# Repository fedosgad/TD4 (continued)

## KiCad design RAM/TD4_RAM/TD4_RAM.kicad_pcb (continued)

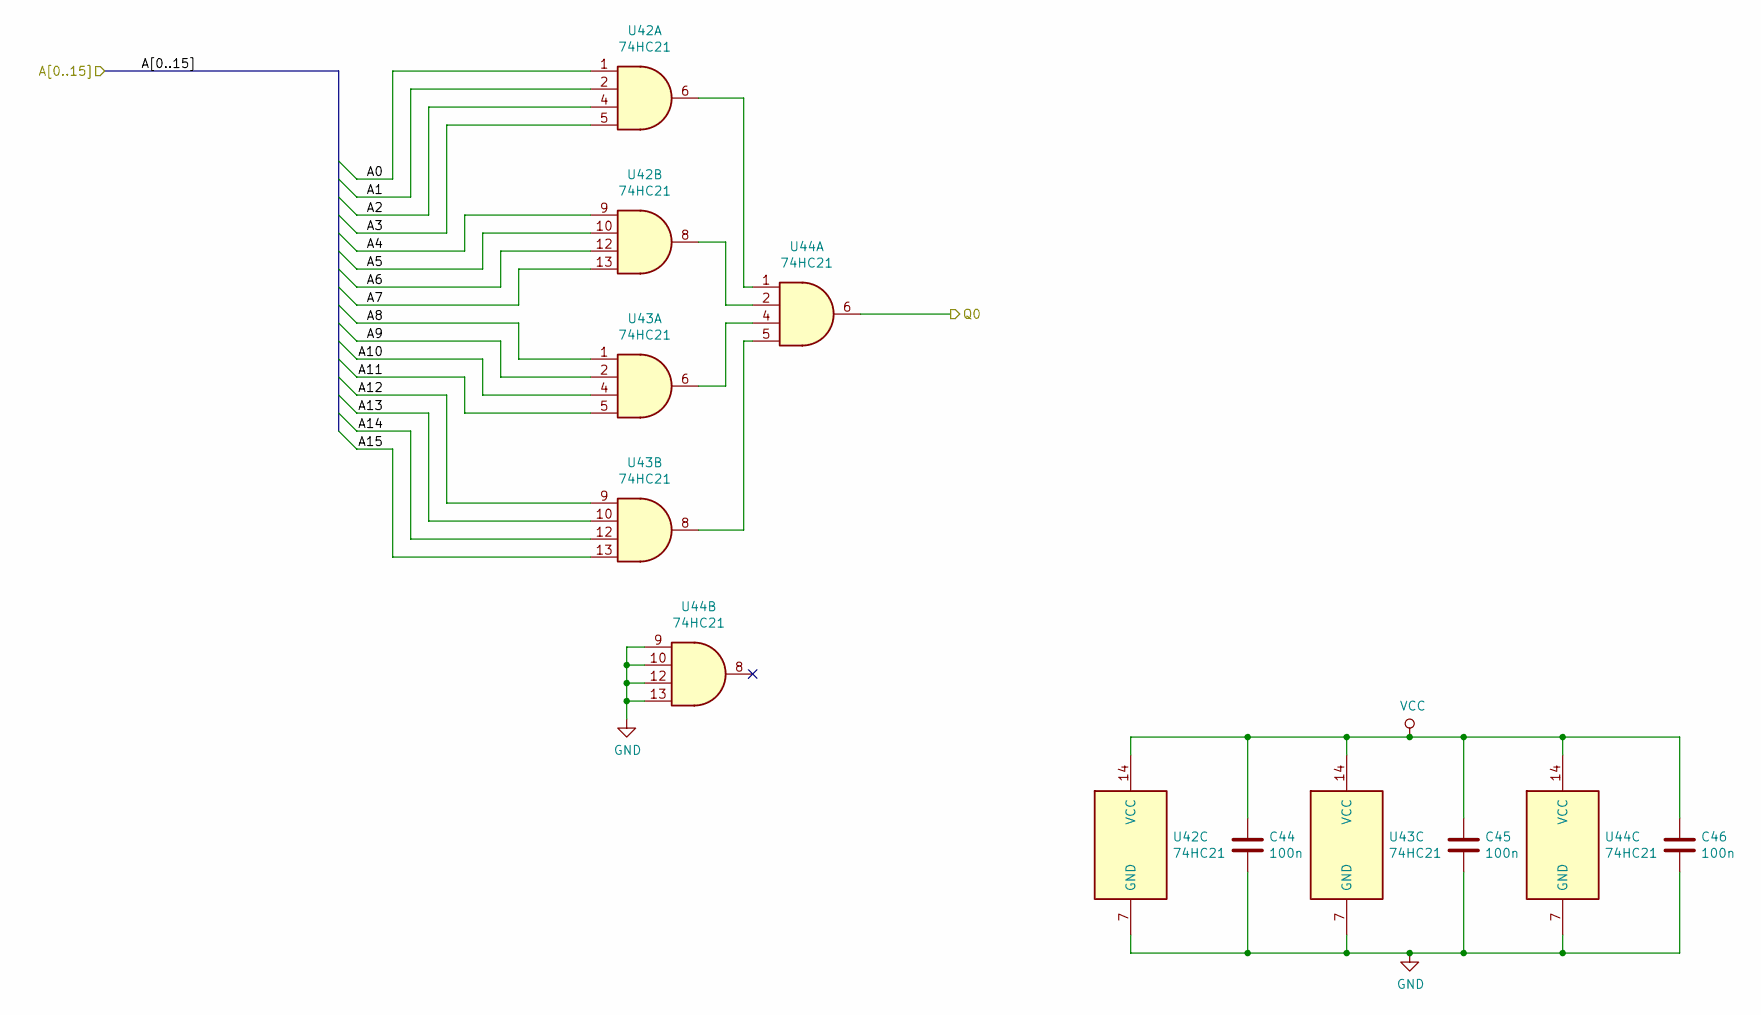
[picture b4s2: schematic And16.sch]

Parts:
C44, C45, C46: 100n; C_0805_2012Metric
U42, U43, U44: 74HC21; SOIC-14_3.9x8.7mm_P1.27mm

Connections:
/sheet5CBA2603/A0: U42.1; also elsewhere on the board
/sheet5CBA2603/A1: U42.2; also elsewhere on the board
/sheet5CBA2603/A2: U42.4; also elsewhere on the board
/sheet5CBA2603/A3: U42.5; also elsewhere on the board
/sheet5CBA2603/A4: U42.9; also elsewhere on the board
/sheet5CBA2603/A5: U42.10; also elsewhere on the board
/sheet5CBA2603/A6: U42.12; also elsewhere on the board
/sheet5CBA2603/A7: U42.13; also elsewhere on the board
/sheet5CBA2603/A8: U43.1; also elsewhere on the board
/sheet5CBA2603/A9: U43.2; also elsewhere on the board
/sheet5CBA2603/A10: U43.4; also elsewhere on the board
/sheet5CBA2603/A11: U43.5; also elsewhere on the board
/sheet5CBA2603/A12: U43.9; also elsewhere on the board
/sheet5CBA2603/A13: U43.10; also elsewhere on the board
/sheet5CBA2603/A14: U43.12; also elsewhere on the board
/sheet5CBA2603/A15: U43.13; also elsewhere on the board
/sheet5CBA2603/Q0: U44.6; also elsewhere on the board
unnamed: U42.6, U44.1
unnamed: U42.8, U44.2
unnamed: U43.6, U44.4
unnamed: U43.8, U44.5
VCC: C44.1, C45.1, C46.1, U42.14 (VCC), U43.14 (VCC), U44.14 (VCC); also elsewhere on the board

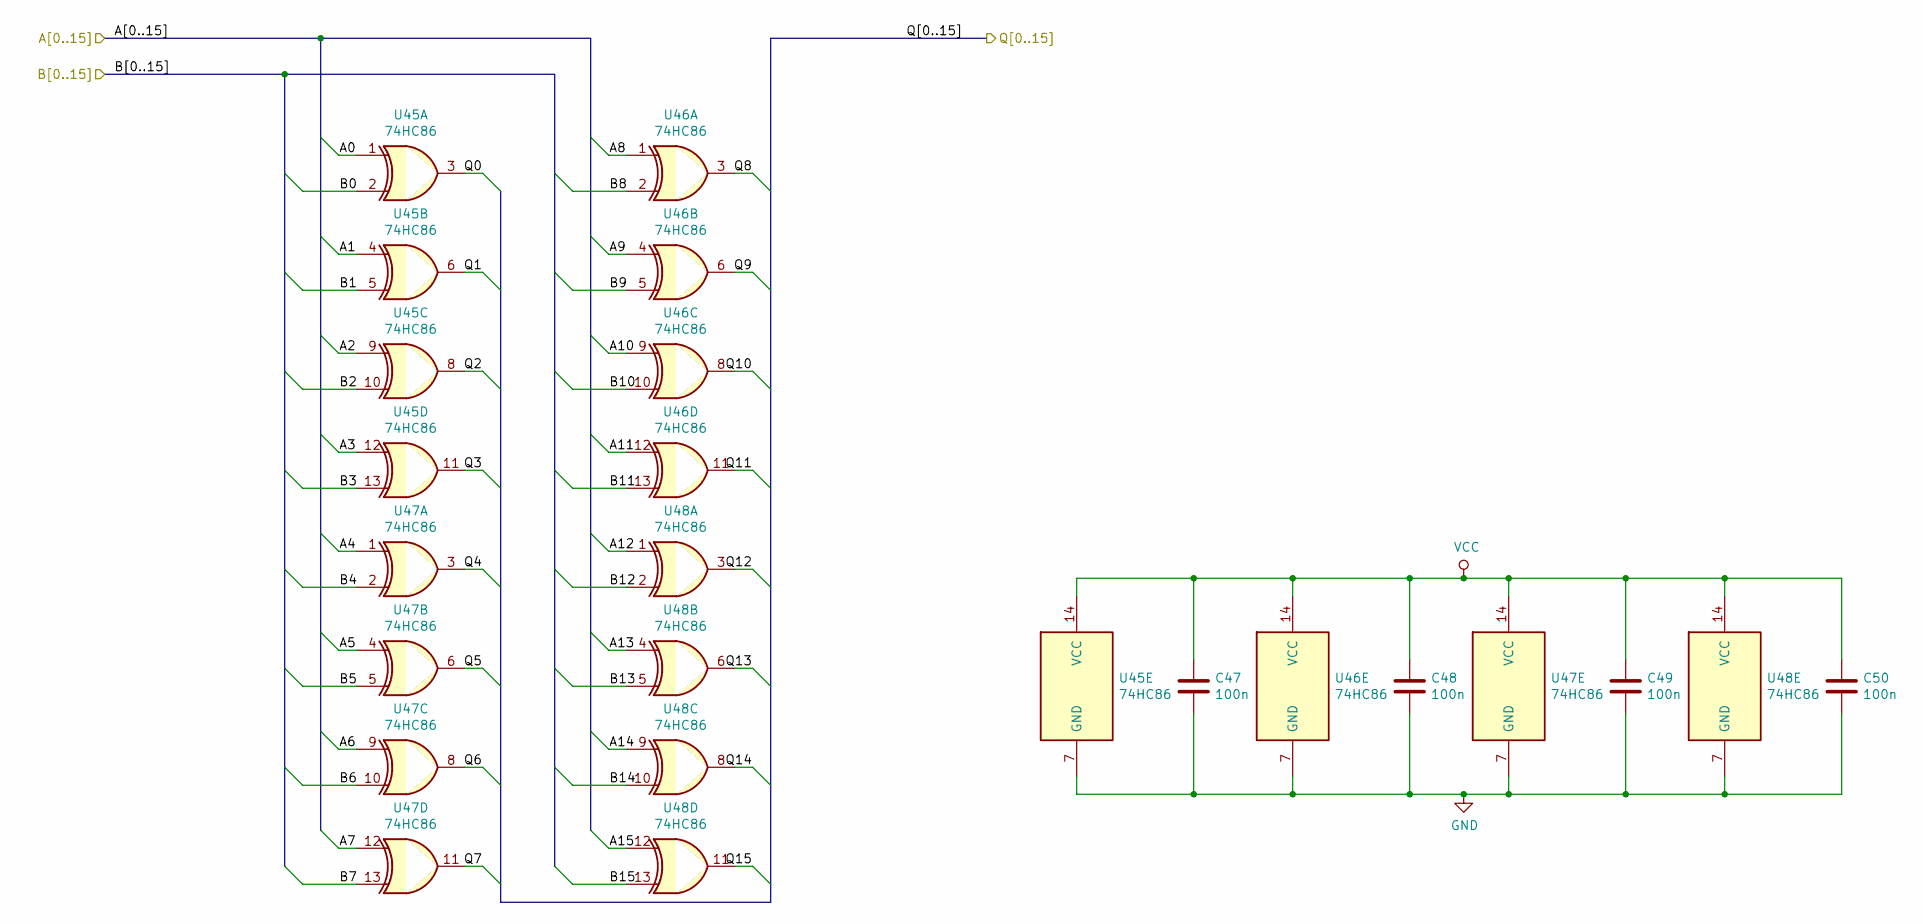
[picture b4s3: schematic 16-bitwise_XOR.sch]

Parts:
C47, C48, C49, C50: 100n; C_0805_2012Metric
U45, U46, U47, U48: 74HC86; SOIC-14_3.9x8.7mm_P1.27mm

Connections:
/sheet5CBA2603/A0: U45.3; also elsewhere on the board
/sheet5CBA2603/A1: U45.6; also elsewhere on the board
/sheet5CBA2603/A2: U45.8; also elsewhere on the board
/sheet5CBA2603/A3: U45.11; also elsewhere on the board
/sheet5CBA2603/A4: U47.3; also elsewhere on the board
/sheet5CBA2603/A5: U47.6; also elsewhere on the board
/sheet5CBA2603/A6: U47.8; also elsewhere on the board
/sheet5CBA2603/A7: U47.11; also elsewhere on the board
/sheet5CBA2603/A8: U46.3; also elsewhere on the board
/sheet5CBA2603/A9: U46.6; also elsewhere on the board
/sheet5CBA2603/A10: U46.8; also elsewhere on the board
/sheet5CBA2603/A11: U46.11; also elsewhere on the board
/sheet5CBA2603/A12: U48.3; also elsewhere on the board
/sheet5CBA2603/A13: U48.6; also elsewhere on the board
/sheet5CBA2603/A14: U48.8; also elsewhere on the board
/sheet5CBA2603/A15: U48.11; also elsewhere on the board
/sheet5CBF05D3/A0: U45.1; also elsewhere on the board
/sheet5CBF05D3/A1: U45.4; also elsewhere on the board
/sheet5CBF05D3/A2: U45.9; also elsewhere on the board
/sheet5CBF05D3/A3: U45.12; also elsewhere on the board
/sheet5CBF05D3/A4: U47.1; also elsewhere on the board
/sheet5CBF05D3/A5: U47.4; also elsewhere on the board
/sheet5CBF05D3/A6: U47.9; also elsewhere on the board
/sheet5CBF05D3/A7: U47.12; also elsewhere on the board
/sheet5CBF05D3/A8: U46.1; also elsewhere on the board
/sheet5CBF05D3/A9: U46.4; also elsewhere on the board
/sheet5CBF05D3/A10: U46.9; also elsewhere on the board
/sheet5CBF05D3/A11: U46.12; also elsewhere on the board
/sheet5CBF05D3/A12: U48.1; also elsewhere on the board
/sheet5CBF05D3/A13: U48.4; also elsewhere on the board
/sheet5CBF05D3/A14: U48.9; also elsewhere on the board
/sheet5CBF05D3/A15: U48.12; also elsewhere on the board
/sheet5CBF05D3/B0: U45.2; also elsewhere on the board
/sheet5CBF05D3/B1: U45.5; also elsewhere on the board
/sheet5CBF05D3/B2: U45.10; also elsewhere on the board
/sheet5CBF05D3/B3: U45.13; also elsewhere on the board
/sheet5CBF05D3/B4: U47.2; also elsewhere on the board
/sheet5CBF05D3/B5: U47.5; also elsewhere on the board
/sheet5CBF05D3/B6: U47.10; also elsewhere on the board
/sheet5CBF05D3/B7: U47.13; also elsewhere on the board
/sheet5CBF05D3/B8: U46.2; also elsewhere on the board
/sheet5CBF05D3/B9: U46.5; also elsewhere on the board
/sheet5CBF05D3/B10: U46.10; also elsewhere on the board
/sheet5CBF05D3/B11: U46.13; also elsewhere on the board
/sheet5CBF05D3/B12: U48.2; also elsewhere on the board
/sheet5CBF05D3/B13: U48.5; also elsewhere on the board
/sheet5CBF05D3/B14: U48.10; also elsewhere on the board
/sheet5CBF05D3/B15: U48.13; also elsewhere on the board
VCC: C47.1, C48.1, C49.1, C50.1, U45.14 (VCC), U46.14 (VCC), U47.14 (VCC), U48.14 (VCC); also elsewhere on the board

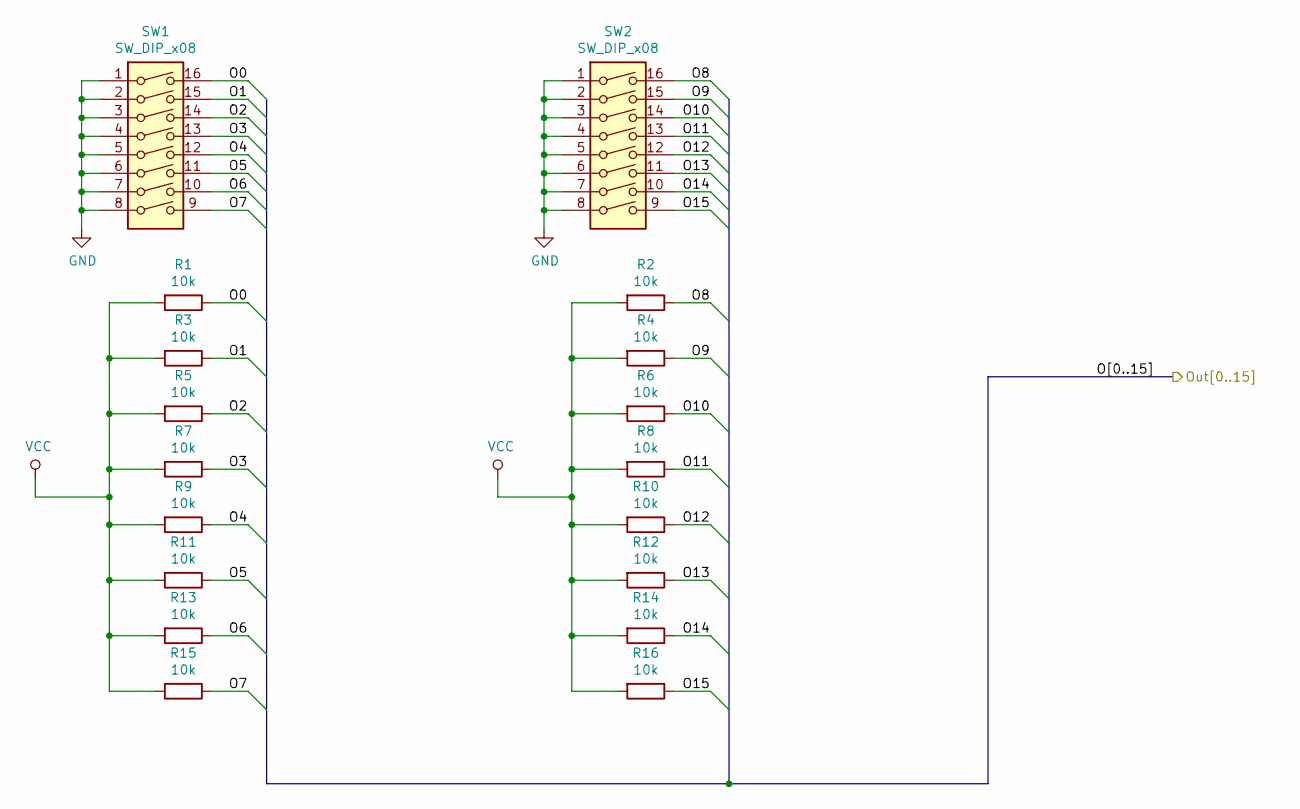
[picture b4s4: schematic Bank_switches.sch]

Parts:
R1, R2, R3, R4, R5, R6, R7, R8, R9, R10, R11, R12, R13, R14, R15, R16: 10k; C_0805_2012Metric
SW1, SW2: SW_DIP_x08; SW_DIP_SPSTx08_Slide_9.78x22.5mm_W7.62mm_P2.54mm

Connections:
/sheet5CBF05D3/A0: R1.1, SW1.16; also elsewhere on the board
/sheet5CBF05D3/A1: R3.1, SW1.15; also elsewhere on the board
/sheet5CBF05D3/A2: R5.1, SW1.14; also elsewhere on the board
/sheet5CBF05D3/A3: R7.1, SW1.13; also elsewhere on the board
/sheet5CBF05D3/A4: R9.1, SW1.12; also elsewhere on the board
/sheet5CBF05D3/A5: R11.1, SW1.11; also elsewhere on the board
/sheet5CBF05D3/A6: R13.1, SW1.10; also elsewhere on the board
/sheet5CBF05D3/A7: R15.1, SW1.9; also elsewhere on the board
/sheet5CBF05D3/A8: R2.1, SW2.16; also elsewhere on the board
/sheet5CBF05D3/A9: R4.1, SW2.15; also elsewhere on the board
/sheet5CBF05D3/A10: R6.1, SW2.14; also elsewhere on the board
/sheet5CBF05D3/A11: R8.1, SW2.13; also elsewhere on the board
/sheet5CBF05D3/A12: R10.1, SW2.12; also elsewhere on the board
/sheet5CBF05D3/A13: R12.1, SW2.11; also elsewhere on the board
/sheet5CBF05D3/A14: R14.1, SW2.10; also elsewhere on the board
/sheet5CBF05D3/A15: R16.1, SW2.9; also elsewhere on the board
VCC: R1.2, R2.2, R3.2, R4.2, R5.2, R6.2, R7.2, R8.2, R9.2, R10.2, R11.2, R12.2, R13.2, R14.2, R15.2, R16.2; also elsewhere on the board

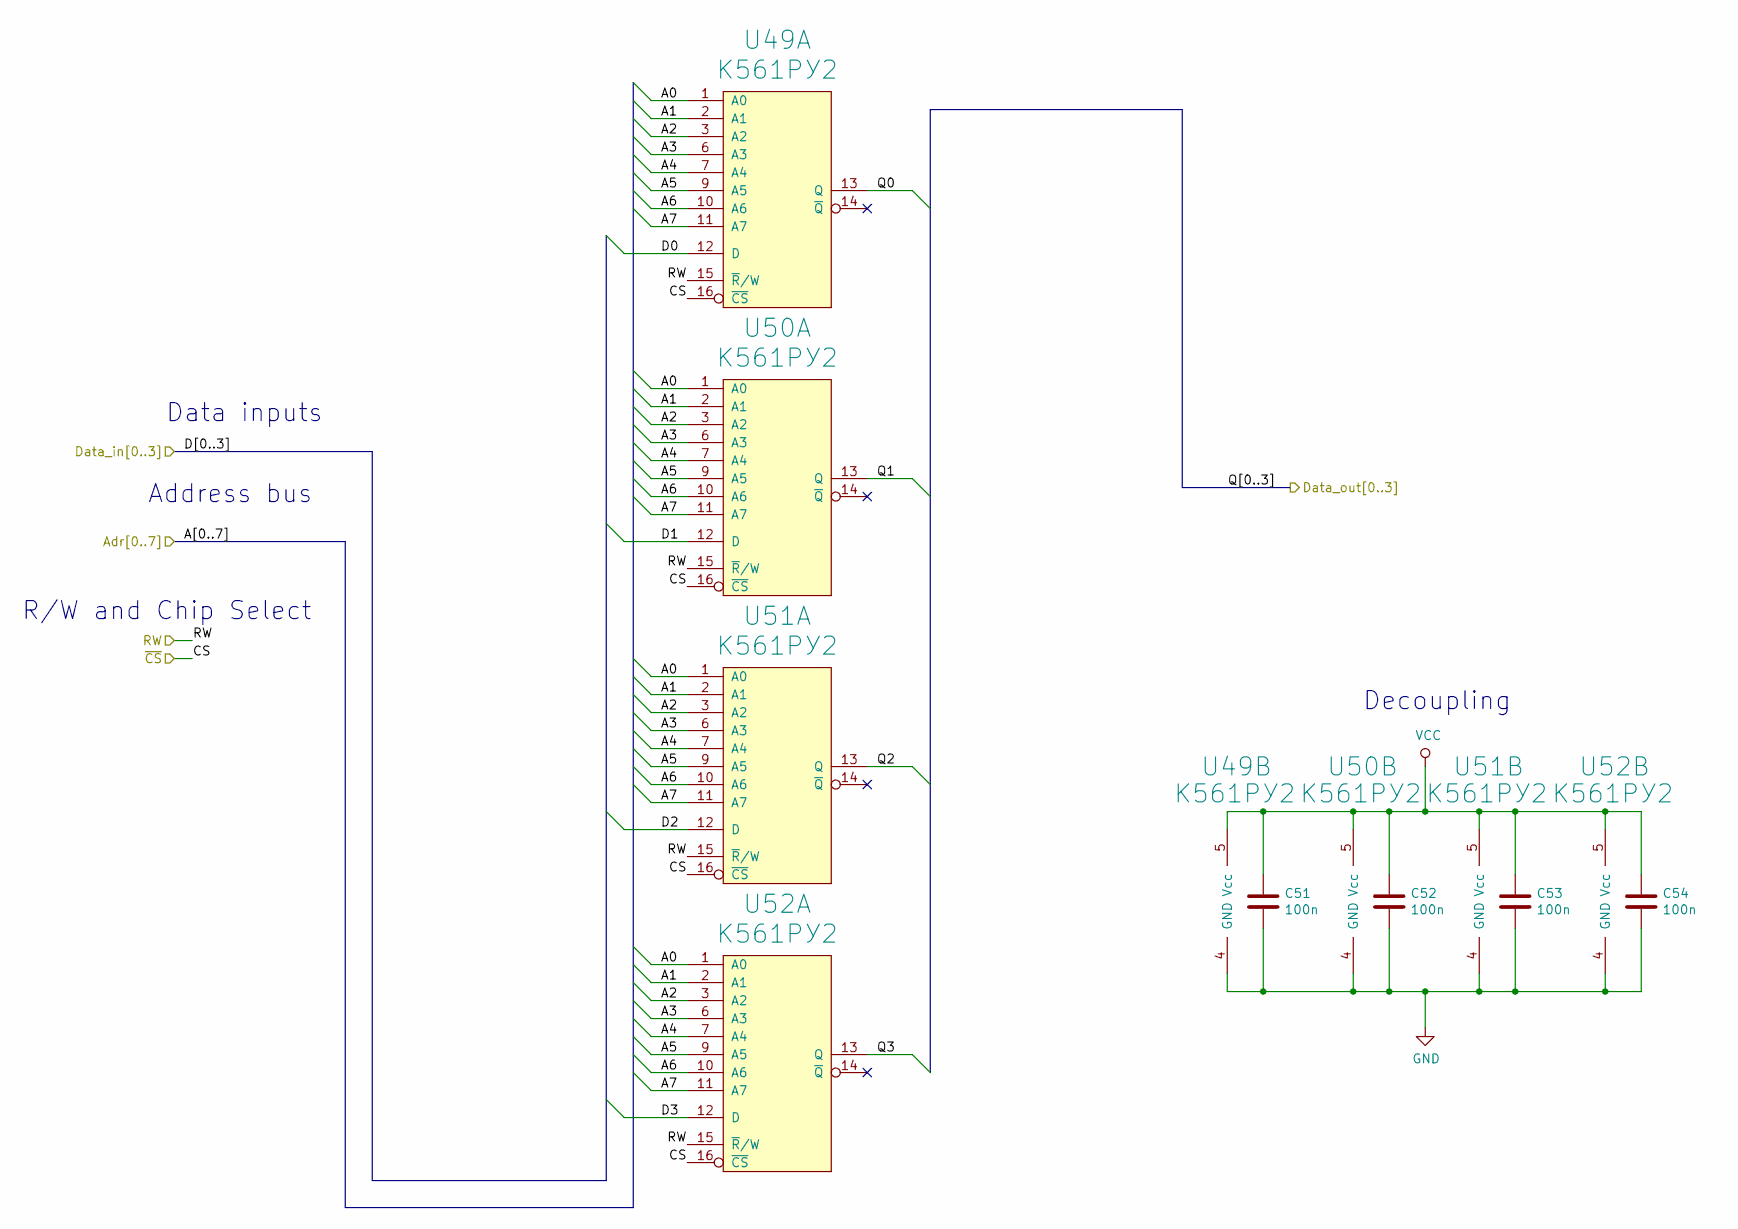
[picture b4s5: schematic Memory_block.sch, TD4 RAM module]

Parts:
C51, C52, C53, C54: 100n; C_0805_2012Metric
U49, U50, U51, U52: К561РУ2; DIP-16_W7.62mm_Socket_LongPads

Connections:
/Memory block/~CS: U49.16 (~CS), U50.16 (~CS), U51.16 (~CS), U52.16 (~CS); also elsewhere on the board
/RAM_A0: U49.1 (A0), U50.1 (A0), U51.1 (A0), U52.1 (A0); also elsewhere on the board
/RAM_A1: U49.2 (A1), U50.2 (A1), U51.2 (A1), U52.2 (A1); also elsewhere on the board
/RAM_A2: U49.3 (A2), U50.3 (A2), U51.3 (A2), U52.3 (A2); also elsewhere on the board
/RAM_A3: U49.6 (A3), U50.6 (A3), U51.6 (A3), U52.6 (A3); also elsewhere on the board
/RAM_A4: U49.7 (A4), U50.7 (A4), U51.7 (A4), U52.7 (A4); also elsewhere on the board
/RAM_A5: U49.9 (A5), U50.9 (A5), U51.9 (A5), U52.9 (A5); also elsewhere on the board
/RAM_A6: U49.10 (A6), U50.10 (A6), U51.10 (A6), U52.10 (A6); also elsewhere on the board
/RAM_A7: U49.11 (A7), U50.11 (A7), U51.11 (A7), U52.11 (A7); also elsewhere on the board
/RAM_RW: U49.15 (~R~/W), U50.15 (~R~/W), U51.15 (~R~/W), U52.15 (~R~/W); also elsewhere on the board
VCC: C51.1, C52.1, C53.1, C54.1, U49.5 (Vcc), U50.5 (Vcc), U51.5 (Vcc), U52.5 (Vcc); also elsewhere on the board

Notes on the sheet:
Address bus
Data inputs
R/W and Chip Select
Decoupling

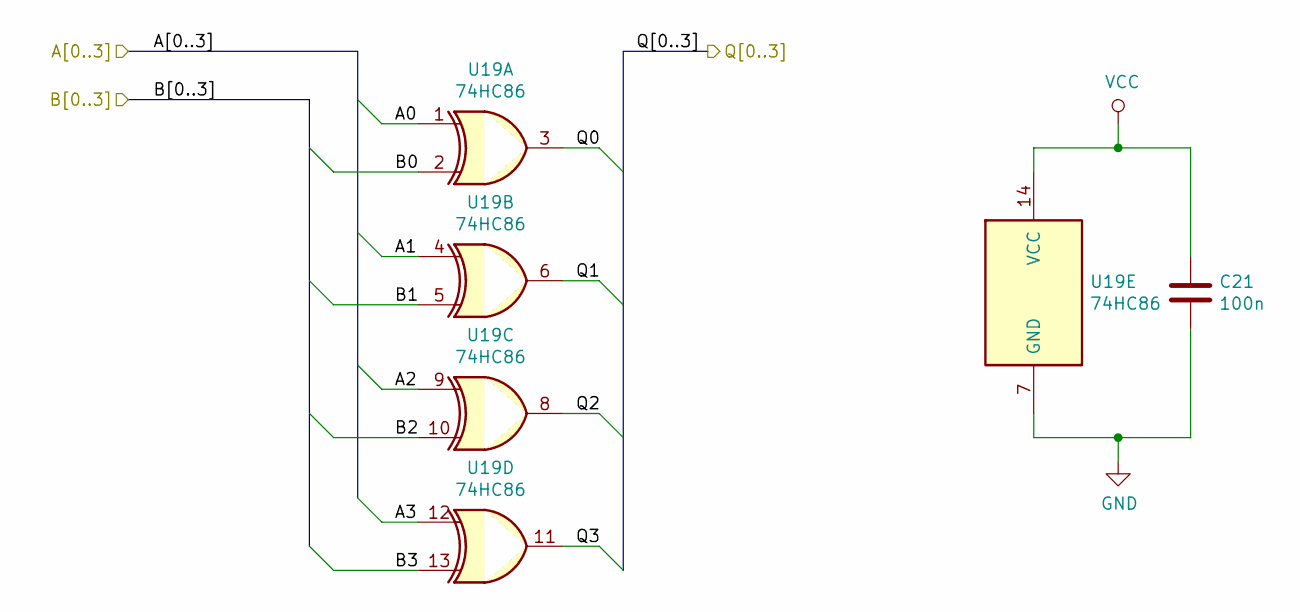
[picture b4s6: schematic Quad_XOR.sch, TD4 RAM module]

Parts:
C4: 100n; C_0805_2012Metric
U2: 74HC86; SOIC-14_3.9x8.7mm_P1.27mm

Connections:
/Address comparator/4-bitwise NOT/A0: U2.3; also elsewhere on the board
/Address comparator/4-bitwise NOT/A1: U2.6; also elsewhere on the board
/Address comparator/4-bitwise NOT/A2: U2.8; also elsewhere on the board
/Address comparator/4-bitwise NOT/A3: U2.11; also elsewhere on the board
/RAM_A4: U2.2; also elsewhere on the board
/RAM_A5: U2.5; also elsewhere on the board
/RAM_A6: U2.10; also elsewhere on the board
/RAM_A7: U2.13; also elsewhere on the board
VCC: C4.1, U2.14 (VCC); also elsewhere on the board

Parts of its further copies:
C7, C8, C9, C10, C11, C12, C13, C14, C15, C16, C17, C18, C19, C20, C21: 100n; C_0805_2012Metric
U5, U6, U7, U8, U9, U10, U11, U12, U13, U14, U15, U16, U17, U18, U19: 74HC86; SOIC-14_3.9x8.7mm_P1.27mm

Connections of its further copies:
/Address comparator/sheet5CCFCFC3/A0: U6.3; also elsewhere on the board
/Address comparator/sheet5CCFCFC3/A1: U6.6; also elsewhere on the board
/Address comparator/sheet5CCFCFC3/A2: U6.8; also elsewhere on the board
/Address comparator/sheet5CCFCFC3/A3: U6.11; also elsewhere on the board
/Address comparator/sheet5CD0A991/A0: U7.3; also elsewhere on the board
/Address comparator/sheet5CD0A991/A1: U7.6; also elsewhere on the board
/Address comparator/sheet5CD0A991/A2: U7.8; also elsewhere on the board
/Address comparator/sheet5CD0A991/A3: U7.11; also elsewhere on the board
/Address comparator/sheet5CD1F070/A0: U16.3; also elsewhere on the board
/Address comparator/sheet5CD1F070/A1: U16.6; also elsewhere on the board
/Address comparator/sheet5CD1F070/A2: U16.8; also elsewhere on the board
/Address comparator/sheet5CD1F070/A3: U16.11; also elsewhere on the board
/Address comparator/sheet5CD1F071/A0: U17.3; also elsewhere on the board
/Address comparator/sheet5CD1F071/A1: U17.6; also elsewhere on the board
/Address comparator/sheet5CD1F071/A2: U17.8; also elsewhere on the board
/Address comparator/sheet5CD1F071/A3: U17.11; also elsewhere on the board
/Address comparator/sheet5CD1F072/A0: U19.3; also elsewhere on the board
/Address comparator/sheet5CD1F072/A1: U19.6; also elsewhere on the board
/Address comparator/sheet5CD1F072/A2: U19.8; also elsewhere on the board
/Address comparator/sheet5CD1F072/A3: U19.11; also elsewhere on the board
/Address comparator/sheet5CD1F073/A0: U18.3; also elsewhere on the board
/Address comparator/sheet5CD1F073/A1: U18.6; also elsewhere on the board
/Address comparator/sheet5CD1F073/A2: U18.8; also elsewhere on the board
/Address comparator/sheet5CD1F073/A3: U18.11; also elsewhere on the board
/Address comparator/sheet5CD03CAA/A0: U5.3; also elsewhere on the board
/Address comparator/sheet5CD03CAA/A1: U5.6; also elsewhere on the board
/Address comparator/sheet5CD03CAA/A2: U5.8; also elsewhere on the board
/Address comparator/sheet5CD03CAA/A3: U5.11; also elsewhere on the board
/Address comparator/sheet5CD1837A/A0: U11.3; also elsewhere on the board
/Address comparator/sheet5CD1837A/A1: U11.6; also elsewhere on the board
/Address comparator/sheet5CD1837A/A2: U11.8; also elsewhere on the board
/Address comparator/sheet5CD1837A/A3: U11.11; also elsewhere on the board
/Address comparator/sheet5CD1837B/A0: U13.3; also elsewhere on the board
/Address comparator/sheet5CD1837B/A1: U13.6; also elsewhere on the board
/Address comparator/sheet5CD1837B/A2: U13.8; also elsewhere on the board
/Address comparator/sheet5CD1837B/A3: U13.11; also elsewhere on the board
/Address comparator/sheet5CD1837C/A0: U15.3; also elsewhere on the board
/Address comparator/sheet5CD1837C/A1: U15.6; also elsewhere on the board
/Address comparator/sheet5CD1837C/A2: U15.8; also elsewhere on the board
/Address comparator/sheet5CD1837C/A3: U15.11; also elsewhere on the board
/Address comparator/sheet5CD1837D/A0: U14.3; also elsewhere on the board
/Address comparator/sheet5CD1837D/A1: U14.6; also elsewhere on the board
/Address comparator/sheet5CD1837D/A2: U14.8; also elsewhere on the board
/Address comparator/sheet5CD1837D/A3: U14.11; also elsewhere on the board
/Address comparator/sheet5CD11684/A0: U9.3; also elsewhere on the board
/Address comparator/sheet5CD11684/A1: U9.6; also elsewhere on the board
/Address comparator/sheet5CD11684/A2: U9.8; also elsewhere on the board
/Address comparator/sheet5CD11684/A3: U9.11; also elsewhere on the board
/Address comparator/sheet5CD11685/A0: U8.3; also elsewhere on the board
/Address comparator/sheet5CD11685/A1: U8.6; also elsewhere on the board
/Address comparator/sheet5CD11685/A2: U8.8; also elsewhere on the board
/Address comparator/sheet5CD11685/A3: U8.11; also elsewhere on the board
/Address comparator/sheet5CD11686/A0: U10.3; also elsewhere on the board
/Address comparator/sheet5CD11686/A1: U10.6; also elsewhere on the board
/Address comparator/sheet5CD11686/A2: U10.8; also elsewhere on the board
/Address comparator/sheet5CD11686/A3: U10.11; also elsewhere on the board
/Address comparator/sheet5CD11687/A0: U12.3; also elsewhere on the board
/Address comparator/sheet5CD11687/A1: U12.6; also elsewhere on the board
/Address comparator/sheet5CD11687/A2: U12.8; also elsewhere on the board
/Address comparator/sheet5CD11687/A3: U12.11; also elsewhere on the board
/RAM_A4: U5.2, U6.2, U7.2, U8.2, U9.2, U10.2, U11.2, U12.2, U13.2, U14.2, U15.2, U16.2, U17.2, U18.2, U19.2; also elsewhere on the board
/RAM_A5: U5.5, U6.5, U7.5, U8.5, U9.5, U10.5, U11.5, U12.5, U13.5, U14.5, U15.5, U16.5, U17.5, U18.5, U19.5; also elsewhere on the board
/RAM_A6: U5.10, U6.10, U7.10, U8.10, U9.10, U10.10, U11.10, U12.10, U13.10, U14.10, U15.10, U16.10, U17.10, U18.10, U19.10; also elsewhere on the board
/RAM_A7: U5.13, U6.13, U7.13, U8.13, U9.13, U10.13, U11.13, U12.13, U13.13, U14.13, U15.13, U16.13, U17.13, U18.13, U19.13; also elsewhere on the board
VCC: C7.1, C8.1, C9.1, C10.1, C11.1, C12.1, C13.1, C14.1, C15.1, C16.1, C17.1, C18.1, C19.1, C20.1, C21.1, U5.4, U5.14 (VCC), U6.1, U6.14 (VCC), U7.1, U7.4, U7.14 (VCC), U8.1, U8.9, U8.14 (VCC), U9.9, U9.14 (VCC), U10.4, U10.9, U10.14 (VCC), U11.12, U11.14 (VCC), U12.1, U12.4, U12.9, U12.14 (VCC), U13.1, U13.12, U13.14 (VCC), U14.1, U14.4, U14.12, U14.14 (VCC), U15.4, U15.12, U15.14 (VCC), U16.9, U16.12, U16.14 (VCC), U17.1, U17.9, U17.12, U17.14 (VCC), U18.1, U18.4, U18.9, U18.12, U18.14 (VCC), U19.4, U19.9, U19.12, U19.14 (VCC); also elsewhere on the board
